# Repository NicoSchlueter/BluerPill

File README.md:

Blue pill like STM32F103 dev board made to practice PCB design in KiCad following some Phil's lab tutorial.
 
# Things to improve
I am pretty happy with the schematic, but the routing on the board could definitly use quite some work.
I definitly underestimated the amount of signals that needed to go to the headers.

The board could probably have been designed as a two layer board as well.

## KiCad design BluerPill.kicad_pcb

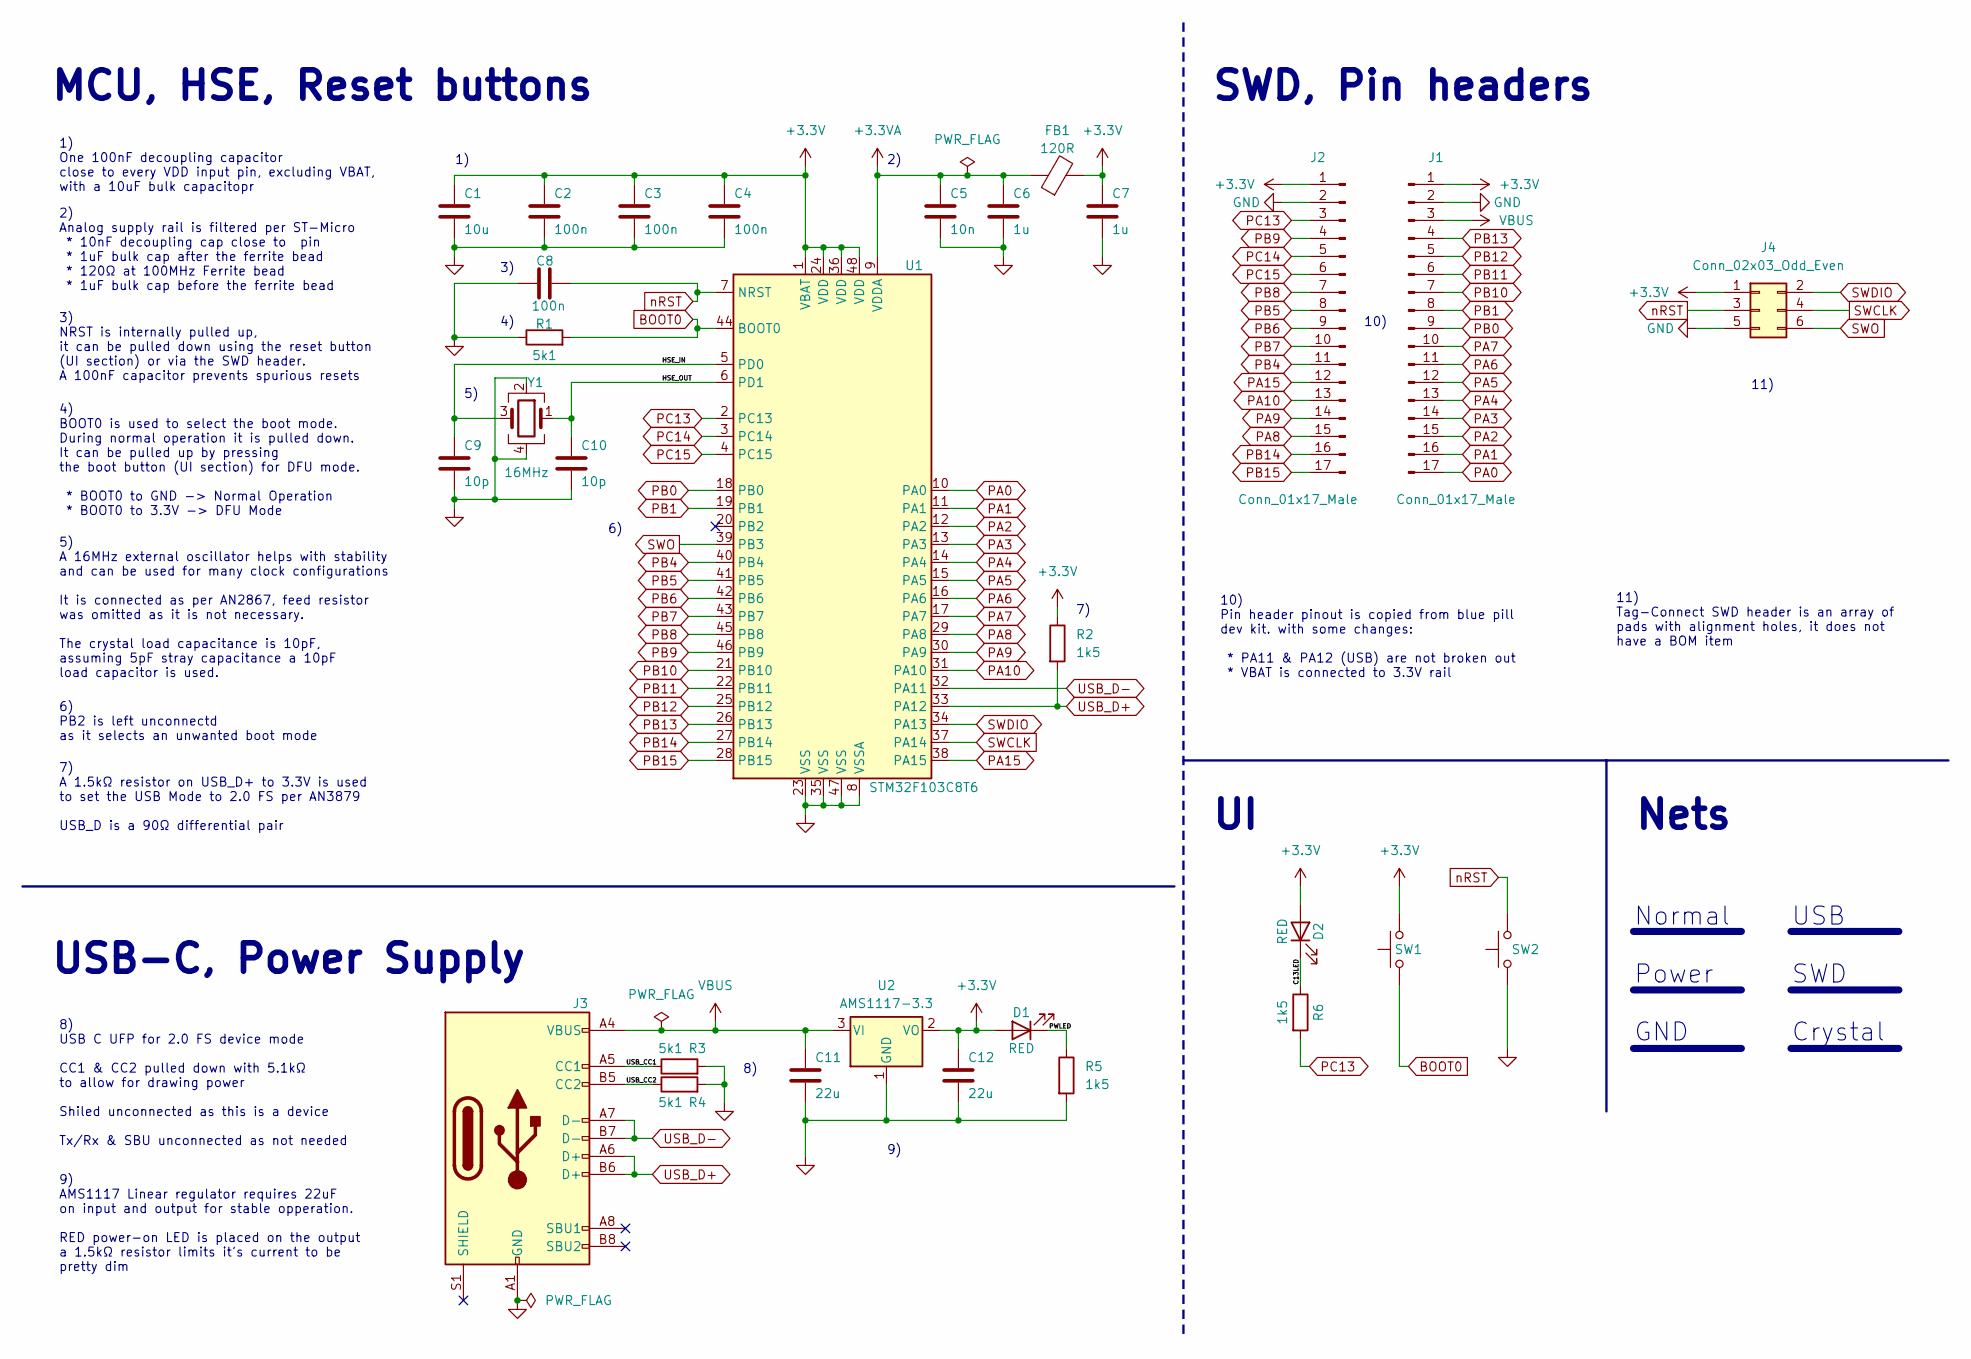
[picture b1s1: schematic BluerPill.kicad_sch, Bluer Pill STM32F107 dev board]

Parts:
C1: 10u; C_0805_2012Metric
C2, C3, C4, C8: 100n; C_0402_1005Metric
C5: 10n; C_0402_1005Metric
C6, C7: 1u; C_0603_1608Metric
C9, C10: 10p; C_0402_1005Metric
C11, C12: 22u; C_0805_2012Metric_Pad1.18x1.45mm_HandSolder
D1, D2: RED; LED_0603_1608Metric
FB1: 120R; L_0603_1608Metric
J1, J2: Conn_01x17_Male; PinHeader_1x17_P2.54mm_Vertical
J3: USB_C_Receptacle_USB2.0; USB_C_Receptacle_HRO_TYPE-C-31-M-12
J4: Conn_02x03_Odd_Even; PinHeader_2x03_P2.54mm_Vertical
R1, R3, R4: 5k1; R_0402_1005Metric
R2, R5, R6: 1k5; R_0402_1005Metric
SW1, SW2: SW_Push; SW_SPST_B3U-1000P
U1: STM32F103C8T6; LQFP-48_7x7mm_P0.5mm
U2: AMS1117-3.3; SOT-223-3_TabPin2
Y1: 16MHz; Crystal_SMD_3225-4Pin_3.2x2.5mm

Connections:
+3.3V: C1.1, C2.1, C3.1, C4.1, C7.1, C12.1, D1.2 (A), D2.2 (A), FB1.2, J1.1, J2.1, J4.1, R2.1, SW1.2, U1.1 (VBAT), U1.24 (VDD), U1.36 (VDD), U1.48 (VDD), U2.2 (VO)
+3.3VA: C5.1, C6.1, FB1.1, U1.9 (VDDA)
/C13LED: D2.1 (K), R6.1
/HSE_IN: C9.1, U1.5 (PD0), Y1.3
/HSE_OUT: C10.1, U1.6 (PD1), Y1.1
/PWLED: D1.1 (K), R5.1
/USB_CC1: J3.A5 (CC1), R3.1
/USB_CC2: J3.B5 (CC2), R4.1
BOOT0: R1.2, SW1.1, U1.44 (BOOT0)
GND: C1.2, C2.2, C3.2, C4.2, C5.2, C6.2, C7.2, C8.2, C9.2, C10.2, C11.2, C12.2, J1.2, J2.2, J3.A1 (GND), J3.A12 (GND), J3.B1 (GND), J3.B12 (GND), J4.5, R1.1, R3.2, R4.2, R5.2, SW2.1, U1.8 (VSSA), U1.23 (VSS), U1.35 (VSS), U1.47 (VSS), U2.1 (GND), Y1.2, Y1.4
PA0: J1.17, U1.10 (PA0)
PA1: J1.16, U1.11 (PA1)
PA2: J1.15, U1.12 (PA2)
PA3: J1.14, U1.13 (PA3)
PA4: J1.13, U1.14 (PA4)
PA5: J1.12, U1.15 (PA5)
PA6: J1.11, U1.16 (PA6)
PA7: J1.10, U1.17 (PA7)
PA8: J2.15, U1.29 (PA8)
PA9: J2.14, U1.30 (PA9)
PA10: J2.13, U1.31 (PA10)
PA15: J2.12, U1.38 (PA15)
PB0: J1.9, U1.18 (PB0)
PB1: J1.8, U1.19 (PB1)
PB4: J2.11, U1.40 (PB4)
PB5: J2.8, U1.41 (PB5)
PB6: J2.9, U1.42 (PB6)
PB7: J2.10, U1.43 (PB7)
PB8: J2.7, U1.45 (PB8)
PB9: J2.4, U1.46 (PB9)
PB10: J1.7, U1.21 (PB10)
PB11: J1.6, U1.22 (PB11)
PB12: J1.5, U1.25 (PB12)
PB13: J1.4, U1.26 (PB13)
PB14: J2.16, U1.27 (PB14)
PB15: J2.17, U1.28 (PB15)
PC13: J2.3, R6.2, U1.2 (PC13)
PC14: J2.5, U1.3 (PC14)
PC15: J2.6, U1.4 (PC15)
SWCLK: J4.4, U1.37 (PA14)
SWDIO: J4.2, U1.34 (PA13)
SWO: J4.6, U1.39 (PB3)
USB_D+: J3.A6 (D+), J3.B6 (D+), R2.2, U1.33 (PA12)
USB_D-: J3.A7 (D-), J3.B7 (D-), U1.32 (PA11)
VBUS: C11.1, J1.3, J3.A4 (VBUS), J3.A9 (VBUS), J3.B4 (VBUS), J3.B9 (VBUS), U2.3 (VI)
nRST: C8.1, J4.3, SW2.2, U1.7 (NRST)

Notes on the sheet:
10) Pin header pinout is copied from blue pill dev kit. with some changes: * PA11 & PA12 (USB) are not broken out * VBAT is connected to 3.3V rail
5) A 16MHz external oscillator helps with stability and can be used for many clock configurations It is connected as per AN2867, feed resistor was omitted as it is not necessary. The crystal load capacitance is 10pF, assuming 5pF stray capacitance a 10pF load capacitor is used.
11) Tag-Connect SWD header is an array of pads with alignment holes, it does not have a BOM item
9) AMS1117 Linear regulator requires 22uF on input and output for stable opperation. RED power-on LED is placed on the output a 1.5kΩ resistor limits it's current to be pretty dim
USB SWD Crystal
Nets
1) One 100nF decoupling capacitor close to every VDD input pin, excluding VBAT, with a 10uF bulk capacitopr
MCU, HSE, Reset buttons
10)
4) BOOT0 is used to select the boot mode. During normal operation it is pulled down. It can be pulled up by pressing the boot button (UI section) for DFU mode. * BOOT0 to GND -> Normal Operation * BOOT0 to 3.3V -> DFU Mode
2) Analog supply rail is filtered per ST-Micro * 10nF decoupling cap close to pin * 1uF bulk cap after the ferrite bead * 120Ω at 100MHz Ferrite bead * 1uF bulk cap before the ferrite bead
8) USB C UFP for 2.0 FS device mode CC1 & CC2 pulled down with 5.1kΩ to allow for drawing power Shiled unconnected as this is a device Tx/Rx & SBU unconnected as not needed
7) A 1.5kΩ resistor on USB_D+ to 3.3V is used to set the USB Mode to 2.0 FS per AN3879 USB_D is a 90Ω differential pair
Normal Power GND
SWD, Pin headers
11)
3) NRST is internally pulled up, it can be pulled down using the reset button (UI section) or via the SWD header. A 100nF capacitor prevents spurious resets
6) PB2 is left unconnectd as it selects an unwanted boot mode
USB-C, Power Supply

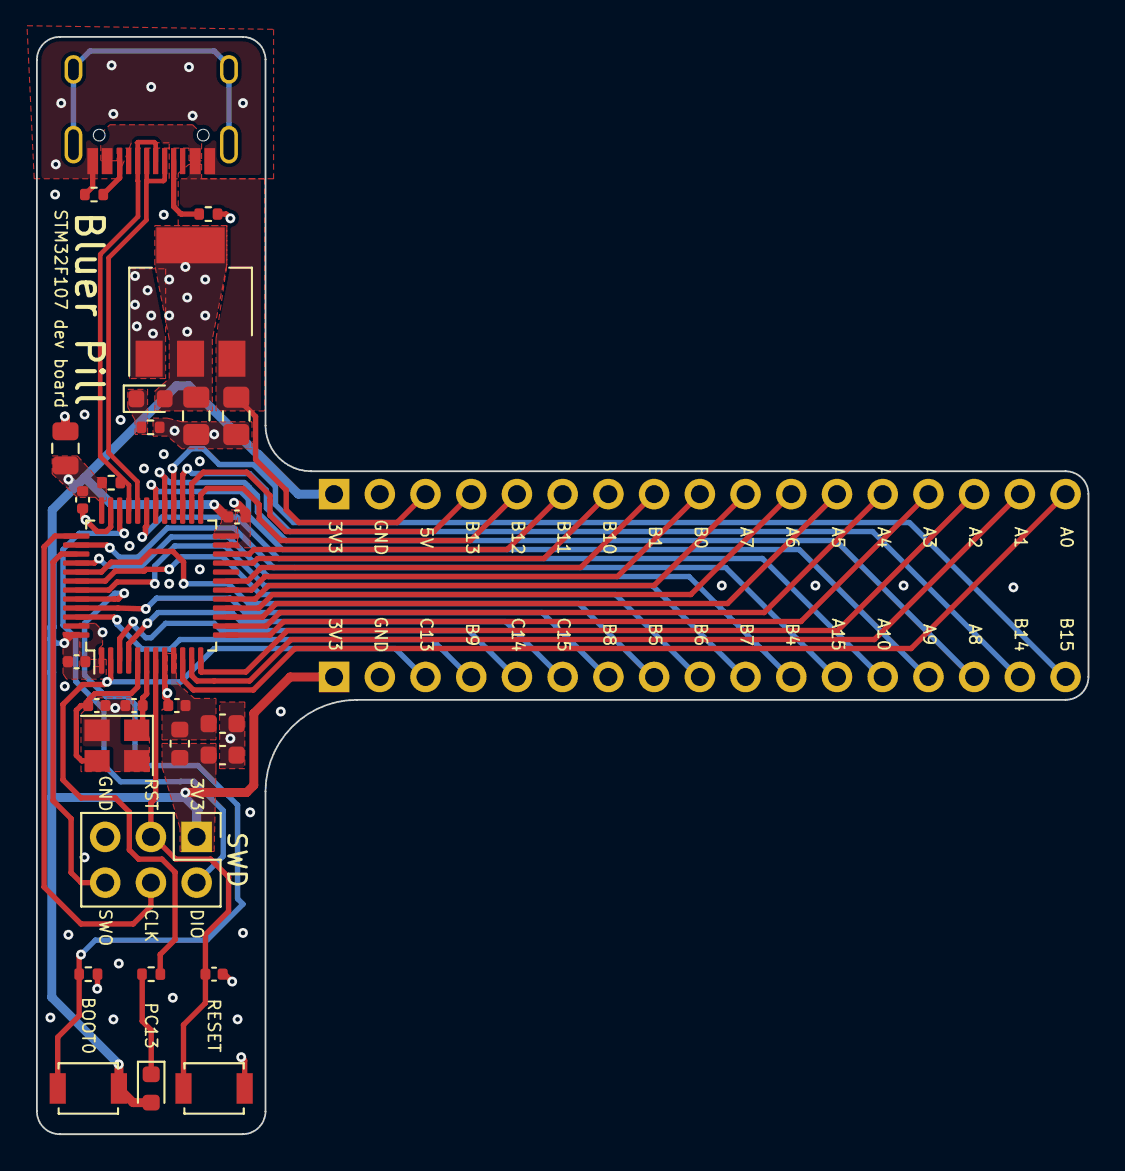
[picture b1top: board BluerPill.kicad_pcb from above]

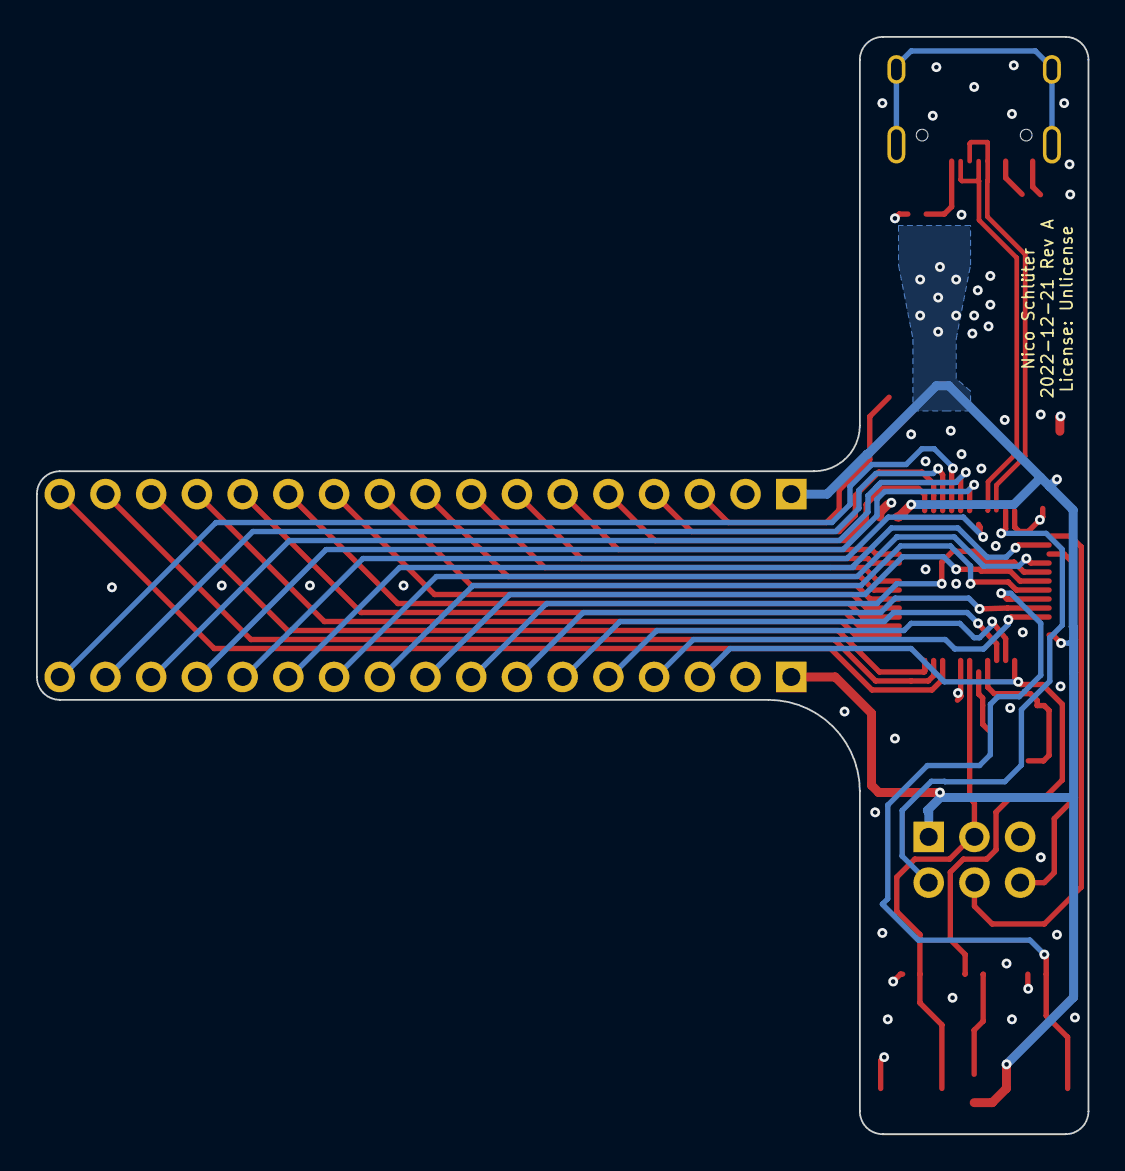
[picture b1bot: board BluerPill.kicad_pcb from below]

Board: 4 copper layers, 58.4 x 61.0 mm, 30 parts (2 on the bottom side), 46 nets.

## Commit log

2022-12-21 Rev A commit

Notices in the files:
BluerPill.kicad_pcb:
License: Unlicense
BluerPill.kicad_sch:
License: unlicense (public domain)
